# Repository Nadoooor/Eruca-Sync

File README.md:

# Eruca-Sync
-------

--------
## Description:
A smart greenhouse with a closed-loop feedback system that can bring stability automatically to the system by itself. It focuses on green leafy plants and on three parameters. <br>

* Light intensity
* Soil moisture
* Temprature<br>

It has actuators that are responible of making the anti-changes that reverse any changes that occur in the environment, like temperature rise, soil drought, and over-light on the green leafy plants.<br>

### Why I am making this:
I made this because there are plants that I really want to try, but I can't plant them in my home because there is no suitable environment for them. So, the project will provide these plants with their suitable environment. For Example, around my home, I can't plant Eruca (Arugula) because of the direct sunlight and the high temperature. I really want to try planting Arugula, so I thought about how to plant it around my home, but with minimal effort. So, I got this idea to make a self-balancing environment for the Arugula or any plant species. 

### Highlight
The light mechanism is the most highlighted actuator here. It is composed of two servos and two pips, which rotate with each other to change different light transmissivity layers to increase the light intensity coming from the sun or decrease it.

## How it works:

1. First, just plug the power plug into any 220V power source. 
2. The screen will light up, asking which plant species you are planting. 
3. Choose the plant species, and that's it.
4. Leave it on its own; it will show you the real-time parameter readings as it is waiting for any changes to power up the actuators.

## Some photos of the project:

### PCB:<br>

### 3D PCB:<br>

### Schematic:

### 3D design:

<br>
<br>
<br>

### IRL Photo:

> [!NOTE]
> Here you are the [Onshape Docs](https://cad.onshape.com/documents/9a096ebca3b52eda8b421bd5/w/291a79fda487721e4172dde6/e/f2d4edb63e0c7f47e937ec7d).
> Also the build journal [here](Docs/Build_Journal.md)

### Fallout Zine  :
<br>

## BOM (Bill of Materials)

---------------------------------------------
| Item Name                                                        | purchase links                                                                                                                                                                                                                                                                                                                                                                                                                                                                                                                                                                                                                                                                                                           | Quantity      | Price Per Unit | Total  |
|------------------------------------------------------------------|----------------------------------------------------------------------------------------------------------------------------------------------------------------------------------------------------------------------------------------------------------------------------------------------------------------------------------------------------------------------------------------------------------------------------------------------------------------------------------------------------------------------------------------------------------------------------------------------------------------------------------------------------------------------------------------------------------------|---------------|----------------|--------|
| FS5106R Servo Motor 360° Continuous 6 kg.cm Plastic Gears        | [Link](https://www.ram-e-shop.com/shop/servo-fs5106r-fs5106r-servo-motor-360deg-continuous-6-kg-cm-plastic-gears-7122)                                                                                                                                                                                                                                                                                                                                                                                                                                                                                                                                                                                         | 2             | $7.4           | $14.8  |
| AM-2320 Temperature & Humidity Calibrated Sensor                 | [Link](https://www.ram-e-shop.com/shop/sen-am2320-am-2320-temperature-humidity-calibrated-sensor-asair-r-original-brand-7776)                                                                                                                                                                                                                                                                                                                                                                                                                                                                                                                                                                                  | 1             | $3.28          | $3.28  |
| NeoPixel Stick 8-bit WS2812 5050 RGB LED                         | [Link](https://www.ram-e-shop.com/shop/kit-ws2812-8-5050-strip-neopixel-stick-8-bit-ws2812-5050-rgb-led-driver-development-board-8257)                                                                                                                                                                                                                                                                                                                                                                                                                                                                                                                                                                         | 6             | $0.84          | $5.04  |
| Capacitive Analog Soil Moisture Sensor V2.0                      | [Link](https://www.ram-e-shop.com/shop/sen-soil-c-capacitive-analog-soil-moisture-sensor-v2-0-sku-soil-c-8116)                                                                                                                                                                                                                                                                                                                                                                                                                                                                                                                                                                                                 | 1             | $1.87          | $1.87  |
| BH1750 Light Calibrated Sensor                                   | [Link](https://ar.aliexpress.com/item/1005009671465215.html?spm=a2g0o.productlist.main.1.395dPm6FPm6Fzx&algo_pvid=c5de86c0-2d13-4ff4-8794-4309014eb837&algo_exp_id=c5de86c0-2d13-4ff4-8794-4309014eb837-0&pdp_ext_f=%7B%22order%22%3A%22471%22%2C%22spu_best_type%22%3A%22price%22%2C%22eval%22%3A%221%22%2C%22fromPage%22%3A%22search%22%7D&pdp_npi=6%40dis%21EGP%21426.75%21110.40%21%21%2155.72%2114.42%21%40214100f417734488518621569e56b7%2112000049823605481%21sea%21EG%210%21ABX%211%210%21n_tag%3A-29910%3Bd%3A2e304f5e%3Bm03_new_user%3A-29895%3BpisId%3A5000000197840371&curPageLogUid=4LlmP7toFGiX&utparam-url=scene%3Asearch%7Cquery_from%3A%7Cx_object_id%3A1005009671465215%7C_p_origin_prod%3A) | 5             | $1.31          | $6.55  |
| Water Pump 3-6Vdc Mini 120L/H                                    | [Link](https://www.ram-e-shop.com/shop/dc-pump-6vdc-water-pump-3-6vdc-mini-120l-h-7422)                                                                                                                                                                                                                                                                                                                                                                                                                                                                                                                                                                                                                        | 1             | $0.84          | $0.84  |
| Thermoelectric Cooler 40x40mm - Peltier                          | [Link](https://www.ram-e-shop.com/shop/sf10080-thermoelectric-cooler-40x40mm-peltier-6726)                                                                                                                                                                                                                                                                                                                                                                                                                                                                                                                                                                                                                     | 1             | $2.81          | $2.81  |
| Aluminum Heatsink HS.13 Size 40x40x11 mm                         | [Link](https://www.ram-e-shop.com/shop/hs13-aluminum-heatsink-hs-13-size-40x40x11-mm-7713)                                                                                                                                                                                                                                                                                                                                                                                                                                                                                                                                                                                                                     | 1             | $0.52          | $0.52  |
| Kit MOSFET 15A 400W - Trigger Switch Drive Module                | [Link](https://www.ram-e-shop.com/shop/kit-mosfet-15a-400w-kit-mosfet-15a-400w-trigger-switch-drive-module-with-pwm-regulator-control-8008)                                                                                                                                                                                                                                                                                                                                                                                                                                                                                                                                                                    | 5             | $0.84          | $4.22  |
| PC Old Power Supply - 200W                                       | [Link](https://www.dubizzle.com.eg/en/electronics-home-appliances/computers-accessories/q-power-supply/)                                                                                                                                                                                                                                                                                                                                                                                                                                                                                                                                                                                                       | 1             | $2             | $2     |
| Old PC CPU Cooler with its Fan                                   | [Link](https://www.dubizzle.com.eg/en/ad/amd-cpu-stock-fan-ID207435960.html)                                                                                                                                                                                                                                                                                                                                                                                                                                                                                                                                                                                                                                   | 1             | $5.62          | $5.62  |
| Old PC Fan 12cm                                                  | [Link](https://www.dubizzle.com.eg/en/ad/%D9%85%D8%B1%D9%88%D8%AD%D8%A9-%D8%A7%D9%84%D9%83%D9%85%D8%A8%D9%8A%D9%88%D8%AA%D8%B1-pc-case-fan-ID207415788.html)                                                                                                                                                                                                                                                                                                                                                                                                                                                                                                                                                   | 1             | $1.56          | $1.56  |
| Water Container (Any bottle or box)                              | [Link](https://www.amazon.eg/-/en/elyassin-plastic-food-container-size/dp/B0C4K14QZV/ref=asc_df_B0C4K14QZV?mcid=f83f3f40348c3aca81581fd755d29a68&tag=egoshpadde-21&linkCode=df0&hvadid=725177773393&hvpos=&hvnetw=g&hvrand=9898077824252821614&hvpone=&hvptwo=&hvqmt=&hvdev=c&hvdvcmdl=&hvlocint=&hvlocphy=9112388&hvtargid=pla-2235574628331&psc=1&language=en_AE&gad_source=1)                                                                                                                                                                                                                                                                                                                               | 1             | $1.3           | $1.3   |
| Wood with the dimensions (all the dimensions are in the onshape) | Bro any Cabinetmaker you don't need a link for that but [At least this will help](https://goodwood.com.eg/en/new-details.php?id=5973) *(For me i used recycled wood from my school)*                                                                                                                                                                                                                                                                                                                                                                                                                                                                                                                           | ~~~           | Vary           | Vary   |
| LCD TFT 2.8 inch Touch Display with ILI9341 Driver 8bit Parallel | [Link](https://www.ram-e-shop.com/shop/kit-lcd-tft-2-8-touch-lcd-tft-2-8-inch-touch-display-for-arduino-uno-mega2560-8003)                                                                                                                                                                                                                                                                                                                                                                                                                                                                                                                                                                                     | 1             | $12.18         | $12.18 |
| ESP32-S3-N16R8 Development Board WIFI and Bluetooth              | [Link](https://mostelectronic.com/shop/arduino-development-boards/esp32-s3-n16r8-development-board-wifi-and-bluetooth/)                                                                                                                                                                                                                                                                                                                                                                                                                                                                                                                                                                                        | 1             | $14.06         | $14.06 |
| PVC pipes as the rotation axies                                  | As well as the wood (plz don't buy it online it is so cheap out there)                                                                                                                                                                                                                                                                                                                                                                                                                                                                                                                                                                                                                                         | 2 x 0.5 meter | $3             | $6     |
| Plastic baggs or plastic sheets                                  | Recycled as well                                                                                                                                                                                                                                                                                                                                                                                                                                                                                                                                                                                                                                                                                               | ~~~           | ~~~            | ~~~    |
| Jumper Wires                                                     | [Link](https://www.ram-e-shop.com/shop/ph61-mm-20cm-ph61-20cm-male-to-male-40-jumper-wires-set-7094)                                                                                                                                                                                                                                                                                                                                                                                                                                                                                                                                                                                                           | 60            | $0.019         | $1.14  |
| Some Nails                                                       | The same place as the pipes                                                                                                                                                                                                                                                                                                                                                                                                                                                                                                                                                                                                                                                                                    | 30            | $0.027         | $0.8   |
| MDF Fast Adhesive Glue                                           | [Link](https://www.amazon.eg/-/en/Akfix-705-Universal-Fast-Adhesive/dp/B07MCQWCQV/ref=sr_1_1?crid=JMZABOFI5Q59&dib=eyJ2IjoiMSJ9.hP0t54WhPBYIvN8RvywzGqQzmqMzmlUrEu0KOEwCDyFlItWe3BiQIYQlq1yIXfjjS0ecLwjxcFoKdVqo_EhPNP86NvI5iyCbqhyLeSCvPZjHmqx9VoXkYTefGrMRnnf0KyayZ9sEV9TGBmlidY9Lgcd1uuuBjttEH5GCcZUDynxih5r3d0zRSV9uq8jcek3OShltEkHc4jghPpo9axMgmGLadUvlVsrWXO3OFKS7u-6tiLPWEWCTFn07oKDck0iPlYYDRP0nvmkYCfUdia9bh31qRD-YmvvLp57fdF0v_p4.mqZp0Uo2UkpAlmg85BgYv_H7G6fkgERg_iH2WGTqdU0&dib_tag=se&keywords=MDF+glue&qid=1779096887&sprefix=mdf+glue%2Caps%2C190&sr=8-1)                                                                                                                                       | 2             | $3.18          | $6.36  |
| PCB | [Link](https://uge-one.com/pcb-print-design/?srsltid=AfmBOopBK8awYYikG2a9qXKbW5DigASPA7Sdrr7dOJ97qQsz4a_aT9M1) | 1 | $20 | $20|
| Shipping                                                         | ~~~~~~~~~~                                                                                                                                                                                                                                                                                                                                                                                                                                                                                                                                                                                                                                                                                                     | ~~~           | ~~~            | $6.74  |
| Total                                                            | ~~~~~~~~~~                                                                                                                                                                                                                                                                                                                                                                                                                                                                                                                                                                                                                                                                                                     | ~~~           | ~~~            | $117.69 |

## How to build the Code:
1. Install PIO (PlatformIO) and clone the repo
2. Open the Eruca-Sync-Code folder, which has the source code in PlatformIO VS Code.
3. Do whatever you want, edit, add, remove, etc.
4. Just click the check mark down there in VS Code to build the code into a .bin and .elf files.
5. Or just click the arrow icon while connecting the ESP to the PC/Laptop to directly compile and upload the code.
6. Enjoy ;)

## How to build the structure:
1. Get wood with the right dimensions(You will find them in the Onshape docs).
2. For the arc on top of the planting area, you can laser cut them along the motor and pipe holders
3. Use the Nails to install all four columns (You can, like, put the nail in its place on the base, and then take it back and cut its head and put it again, and then install the column using a hammer as I did with mine)
4. When you finish the structure using nails and wood, you can then take the fan part, and first you should cut a thin wood rectangle piece(like in the 3D), and then nail the two short columns on top of its sides.
5. Screw the PC fan and the PC cooling part 
6. After that, install the full piece with the same method as the regular columns.
7. Install the wooden planting area, which has the arc and columns on top. (with the same techniques).
8. Put the light sensor and the temperature in the middle of any side of the planting area. (you can use two lil screw or MDF glue).
9. Put the soil in the planting area (And place the soil moisture sensor in the middle of it).
10. You can connect the four outer columns with tall wooden horizontal pieces to make it stable if it is not.
11. Make two identical Rectangles for the roof with the dimensions.
12. Place them at a 30-degree angle from the horizontal so they can make a triangle with each other.
13. Install the Control Panel box on the front side of the structure at an angle of 45 degrees with two small wooden pieces under it to make it stable. (Glue the box to those pieces with MDF and use a nail on the other side in the two little columns.
14. Add the PCB and wire everything to its place on the PCB.
15. Place the power supply and the water container.
16. Use plastic bags or acrylic sheets to cover the greenhouse.
17. Upload the code 
18. That's it, enjoy. ❤️
-----------------

# Made with ❤️ By Nadooor

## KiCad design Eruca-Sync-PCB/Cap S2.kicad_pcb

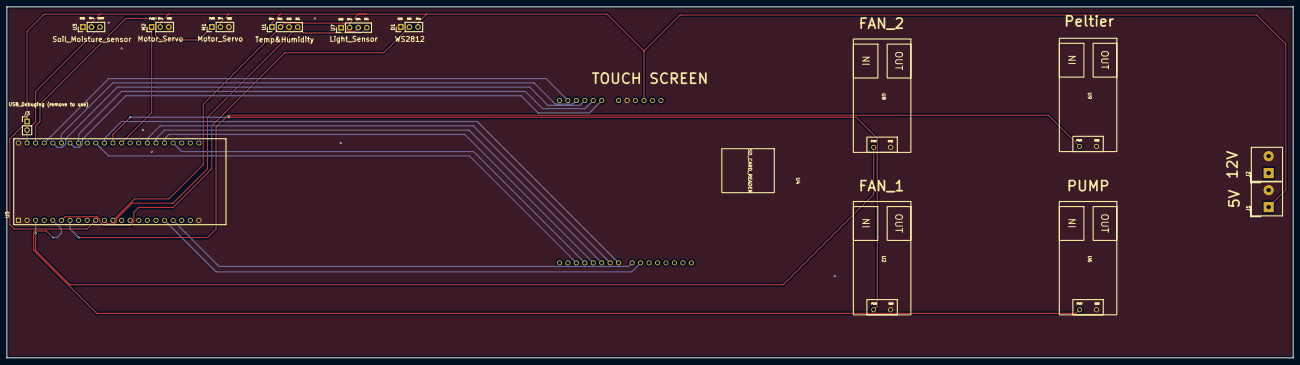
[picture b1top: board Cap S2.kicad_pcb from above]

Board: 2 copper layers, 380.2 x 103.7 mm, 15 parts (0 on the bottom side), 27 nets.

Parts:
D1: WS2812; PinHeader_1x03_P2.54mm_Vertical
J1: 5v&GND; Altech_AK100_1x02_P5.00mm
J2: 12v&GND; Altech_AK100_1x02_P5.00mm
J3: USB_Debuging (remove to use); PinHeader_1x02_P2.54mm_Vertical
M1, M2: Motor_Servo; PinHeader_1x03_P2.54mm_Vertical
U1: Temp&Humidity; PinHeader_1x04_P2.54mm_Vertical
U2: Fan1; MOSFET_KIT
U3: Soil_Moisture_sensor; PinHeader_1x03_P2.54mm_Vertical
U4: TFT_ILI9341_arduino_Sheid; TFT_SCREEN
U5: ESP32-S3; ESP32-S3-DEVKITC-1
U6: Pump; MOSFET_KIT
U7: Light_Sensor; PinHeader_1x04_P2.54mm_Vertical
U8: Fan2; MOSFET_KIT
U9: Platier; MOSFET_KIT

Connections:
5v+: D1.3 (VCC), J1.1, J3.1, M1.2 (+), M2.2 (+), U1.1 (VDD), U3.2 (VCC), U4.10 (5V), U7.2 (VCC)
Fan1: U2.2 (PWM+), U5.33 (GPIO18)
Fan2: U5.3 (GPIO19/USB_D-), U8.2 (PWM+)
GND: D1.1 (VSS), J1.2, J2.2, M1.3 (-), M2.3 (-), U1.3 (GND), U2.1 (GND), U3.1 (GND), U4.8 (GND), U5.1 (GND), U5.2 (GND), U5.22 (GND), U5.44 (GND), U6.1 (GND), U7.1 (GND), U8.1 (GND), U9.1 (GND)
LCD0: U4.20 (LCD_D0), U5.19 (GPIO1)
LCD1: U4.19 (LCD_D1), U5.18 (GPIO2)
LCD2: U4.26 (LCD_D2), U5.35 (GPIO3)
LCD3: U4.25 (LCD_D3), U5.26 (GPIO4)
LCD4: U4.24 (LCD_D4), U5.27 (GPIO5)
LCD5: U4.23 (LCD_D5), U5.28 (GPIO6)
LCD6: U4.22 (LCD_D6), U5.29 (GPIO7)
LCD7: U4.21 (LCD_D7), U5.34 (GPIO8)
LCD_CS: U4.3 (LCD_CS), U5.39 (GPIO11)
LCD_RD: U4.6 (LCD_RD), U5.38 (GPIO10)
LCD_RS: U4.4 (LCD_RS), U5.40 (GPIO12)
LCD_RST: U4.2 (LCD_RST), U5.41 (GPIO13)
LCD_WR: U4.5 (LCD_WR), U5.37 (GPIO9)
Mois_Dout: U3.3 (AUOUT), U5.10 (GPIO35)
unnamed: J3.2, U5.43 (VDDA)
unnamed: U5.23 (VDD3P3), U5.24 (VDD3P3)
Platier: U5.7 (SPICLK_N), U9.2 (PWM+)
Pump: U5.5 (GPIO21), U6.2 (PWM+)
RGB: D1.2 (DIN), U5.6 (SPICLK_P)
SCL_light: U1.4 (SCL), U5.11 (GPIO36), U7.4 (SCL)
SDA_light: U1.2 (SDA), U5.12 (GPIO37), U7.3 (SDA)
Servo1: M1.1 (PWM), U5.42 (GPIO14)
Servo2: M2.1 (PWM), U5.32 (GPIO17)

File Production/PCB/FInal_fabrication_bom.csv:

Designator,Footprint,Quantity,Value,LCSC Part #
D1,PinHeader_1x03_P2.54mm_Vertical,1,WS2812,
J1,Altech_AK100_1x02_P5.00mm,1,5v&GND,
J2,Altech_AK100_1x02_P5.00mm,1,12v&GND,
J3,PinHeader_1x02_P2.54mm_Vertical,1,USB_Debuging (remove to use),
"M1, M2",PinHeader_1x03_P2.54mm_Vertical,2,Motor_Servo,
U1,PinHeader_1x04_P2.54mm_Vertical,1,Temp&Humidity,
U2,MOSFET_KIT,1,Fan1,
U3,PinHeader_1x03_P2.54mm_Vertical,1,Soil_Moisture_sensor,
U4,TFT_SCREEN,1,TFT_ILI9341_arduino_Sheid,
U5,ESP32-S3-DEVKITC-1,1,ESP32-S3,
U6,MOSFET_KIT,1,Pump,
U7,PinHeader_1x04_P2.54mm_Vertical,1,Light_Sensor,
U8,MOSFET_KIT,1,Fan2,
U9,MOSFET_KIT,1,Platier,

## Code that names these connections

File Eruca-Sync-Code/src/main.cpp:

#include <Arduino.h>
#include <Wire.h>
#include <TFT_eSPI.h>       
#include <TouchScreen.h>
#include <BH1750.h>
#include <ESP32Servo.h>
#include <Adafruit_NeoPixel.h>
#include <Adafruit_AM2320.h>
  

#define YP 12 
#define XM 11 
#define YM 1  
#define XP 2  

#define I2C_SDA 37
#define I2C_SCL 36

#define Peliter_pin 48
#define NEOs_pin 47
#define FAN1_pin 16
#define FAN2_pin 17
#define PUMP_pin 21
#define Soil_pin 35
#define ServoL_pin 14
#define ServoR_pin 17

TouchScreen ts = TouchScreen(XP, YP, XM, YM, 300);
TFT_eSPI tft = TFT_eSPI();
BH1750 lightMeter;
Adafruit_AM2320 am;
Servo ServoL;
Servo ServoR;
Adafruit_NeoPixel pixels(48, NEOs_pin, NEO_GRB + NEO_KHZ800);
float currentTemp = 0;
float currentMoist = 0;
float currentLux = 0;

bool tempStatus = false;
bool moistStatus = false;
bool lightStatus = false;

enum SYSMOD{MENU, ARGULA, SPINACH};

SYSMOD sysmod = MENU;

//Parameters  and limits for the feedback system

int mode = 0; //0 for spinach, 1 for argula

float targetTemp = 0;
float min_temp = 0; 
float max_temp = 0;
float targetMoist = 0;
float targetlux = 0; 
float min_lux = 0;
float max_lux = 0;
int irrigation_time = 0;

float Argula_targetTemp = 20.0;
float Argula_min_temp = 18.0; 
float Argula_max_temp = 22.0;
float Argula_targetMoist = 60.0;
float Argula_targetlux = 10800; 
float Argula_min_lux = 9990;
float Argula_max_lux = 11610;
int Argula_irrigation_time = 11800;
int currentlevel = 0; 

//temp
float Spinach_targetTemp = 25.0;
float Spinach_min_temp = 23.0; 
float Spinach_max_temp = 27.0;

//moisture
float Spinach_targetMoist = 70.0;
//light
float Spinach_targetlux = 8100; 
float Spinach_min_lux = 7290;
float Spinach_max_lux = 8910;
float Spinach_irrigation_time = 18610;



float calibed_soil(float raw){
    float calibed = map(raw,3241,1491,0,100);
    if (calibed < 0){
      calibed = 0;
    }
    else if (calibed > 100){
      calibed = 100;
    }
    
      return calibed;
    
}

float calibed_lux(float raw){
    return 0.9985 * raw;
}

float calibed_temp(float raw){
    return 1.054 *raw - 0.2272;
}


float measurePtemp(class Adafruit_AM2320 am){
    return calibed_temp(am.readTemperature());
}

float measurelight(class BH1750 lightMeter){
    return calibed_lux(lightMeter.readLightLevel());
}
float measuremoist(){
    return calibed_soil(analogRead(Soil_pin));
}


void statics(){
    tft.fillScreen(TFT_BLACK);
    tft.fillRect(0, 0, 320, 35, TFT_NAVY);
    tft.setTextColor(TFT_WHITE);
    tft.drawCentreString("Eruca Sync", 160, 8, 2);
    tft.drawFastHLine(0, 85, 300, TFT_SILVER);
    tft.drawFastHLine(0, 140, 300, TFT_SILVER);

    tft.drawFastVLine(160, 45, 145, TFT_SILVER);
    tft.setTextColor(TFT_WHITE);
    tft.drawString("TEMP:",15, 45, 2);
    tft.drawString("MOIST:", 170, 45, 2);
    tft.drawString("LUX:", 15, 95, 2);
    tft.drawString("ACTUATORS:", 170, 95, 2);
}


void menu(){
    tft.fillScreen(TFT_BLACK);
    tft.setTextColor(TFT_WHITE);
    tft.drawCentreString("Select Plant", 160, 40, 4);


    tft.fillRect(20, 100, 130, 80, TFT_DARKGREEN);
    tft.fillRect(20,100,130,80, TFT_WHITE);
    tft.drawCentreString("Argula", 85, 130, 2);

    tft.fillRect(170, 100, 130, 80, TFT_MAROON);
    tft.fillRect(170,100,130,80, TFT_WHITE);  
    tft.drawCentreString("Spinach", 235, 130, 2);  

}


void refreash(){
    tft.setTextColor(TFT_CYAN, TFT_BLACK);
    tft.drawString(String(currentTemp, 1) + " C", 15, 60, 4);
    tft.setTextColor(TFT_BLUE, TFT_BLACK);
    tft.drawString(String(currentMoist, 1) + " %", 170, 60, 4);
    tft.setTextColor(TFT_YELLOW, TFT_BLACK);
    tft.drawString(String(currentLux, 0) + " lx", 15, 110, 4);

    tft.setTextSize(1);
    tft.setTextColor(tempStatus ? TFT_GREEN : TFT_RED, TFT_BLACK);
    tft.drawString(tempStatus ? "Cooling: ON" : "Cooling: OFF", 170, 115, 2);
    tft.setTextColor(moistStatus ? TFT_GREEN : TFT_RED, TFT_BLACK);
    tft.drawString(moistStatus ? "Irrigation: ON" : "Irrigation: OFF", 170, 135, 2);
    tft.setTextColor(lightStatus ? TFT_GREEN : TFT_RED, TFT_BLACK); 
    tft.drawString(lightStatus ? "Shading: ON" : "Shading: OFF", 170, 155, 2);

}



void logic(){
    //temp_logic
    if (mode == 1){
    targetlux = Argula_targetlux;
    targetMoist = Argula_targetMoist;
    targetTemp = Argula_targetTemp;

    max_lux = Argula_max_lux;
    min_lux = Argula_min_lux;

    max_temp = Argula_max_temp;
    min_temp = Argula_min_temp;
    irrigation_time = Argula_irrigation_time;
    }
    else if (mode == 0){
    targetlux = Spinach_targetlux;
    targetMoist = Spinach_targetMoist;
    targetTemp = Spinach_targetTemp;

    max_lux = Spinach_max_lux;
    min_lux = Spinach_min_lux;

    max_temp = Spinach_max_temp;
    min_temp = Spinach_min_temp;

    irrigation_time = Spinach_irrigation_time;
    
}

if(currentTemp > max_temp){
    analogWrite(FAN1_pin, 255);
    analogWrite(FAN2_pin, 255);
    analogWrite(Peliter_pin, 255);
    tempStatus = true;
    
}
else if (currentTemp < min_temp){
    analogWrite(FAN1_pin, 0);
    analogWrite(FAN2_pin, 0);
    analogWrite(Peliter_pin, 0);
    tempStatus = false;
} else {
    Serial.println("There is a problem with the temperature sensor");
}


if (currentMoist < 50 && currentMoist > 10){
    moistStatus = true;
    analogWrite(PUMP_pin, 255);
    delay(irrigation_time);
    analogWrite(PUMP_pin, 0);
    moistStatus = false;
} else if (currentMoist <= 10){
    analogWrite(PUMP_pin, 0);
    moistStatus = false;
} else if (currentMoist >= 85){
    analogWrite(PUMP_pin, 0);
    moistStatus = false;
}

if (currentLux < min_lux && currentLux >= 0){
    if(currentlevel > 0){
        lightStatus = true;
        ServoL.write(45); ServoR.write(135);
        currentlevel--;
        delay(9500);
        ServoL.write(90); ServoR.write(90);
        lightStatus = false;
    
    } else if (currentlevel == 0){
        for (int i = 0; i < 48; i++){
            pixels.setPixelColor(i, pixels.Color(128, 0, 32));
            pixels.show();
            delay(50);
        }
    }

} else if (currentLux > max_lux && currentlevel< 4){
    for (int i = 0; i < 48; i++){
            pixels.setPixelColor(i, pixels.Color(0, 0, 0));
            pixels.show();
            delay(50);
        }
        lightStatus = true;
    ServoL.write(135); ServoR.write(45);
    currentlevel++;
    delay(9500);
    ServoL.write(90); ServoR.write(90);
    lightStatus = false;
} else {
    ServoL.write(90); ServoR.write(90);
    lightStatus = false;
}



}

void setup() {
    Serial.begin(115200);
    tft.init();
    tft.setRotation(3);

    pinMode(Peliter_pin, OUTPUT);
    pinMode(FAN1_pin, OUTPUT);
    pinMode(FAN2_pin, OUTPUT);
    pinMode(PUMP_pin, OUTPUT);
    pinMode(Soil_pin, INPUT);
    pinMode(NEOs_pin, OUTPUT);
    ServoL.attach(ServoL_pin);
    ServoR.attach(ServoR_pin);
    pixels.begin();
    pixels.setBrightness(100);

    Wire.begin(I2C_SDA, I2C_SCL, 100000);
    am.begin();
    lightMeter.begin(BH1750::CONTINUOUS_HIGH_RES_MODE, 0x23, &Wire);
    menu();
}

void loop() {
    if (sysmod == MENU){
        TSPoint p = ts.getPoint();

        pinMode(XP, OUTPUT);
        pinMode(YP, OUTPUT);

        if (p.z > ts.pressureThreshhold){

            int16_t x_calibed = map(p.x, 390, 3683, 0, 320);
            int16_t y_calibed = map(p.y, 3408, 471, 0, 240);

            if (x_calibed > 20 && x_calibed < 150 && y_calibed > 100 && y_calibed < 180){
                mode = 1;
                sysmod = ARGULA;
                tft.fillScreen(TFT_BLACK);
                statics();
            } else if (x_calibed > 170 && x_calibed < 300 && y_calibed > 100 && y_calibed < 180){
                mode = 0;
                sysmod = SPINACH;
                tft.fillScreen(TFT_BLACK);
                statics();
            }

        }





    }else {
    float Stemp = 0;
    float Slux = 0;
    float Smoist = 0;

    for (int i = 0; i < 3; i++){
        Stemp += measurePtemp(am);
        Slux += measurelight(lightMeter);
        Smoist += measuremoist();
        delay(1000);
    }
    currentTemp = Stemp/3;
    currentLux = Slux/3;
    currentMoist = Smoist/3;
    refreash();


    logic();
    }
}

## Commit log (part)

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2026-05-18 Init PIO project
2026-05-18 just changed the folder name
2026-05-18 Wrote all the Logic and the hardcoded parameters
2026-05-18 Finished also the UI of the screen and touch functionality to choose the mode
2026-05-18 built the firmware
2026-05-18 Added the BOM
2026-05-18 Added the PCB and putted the production files in one folder
2026-05-18 BOM edit
2026-05-18 Added photos and made the Readme
2026-05-18 Oops,, forgot the schematic photo
2026-05-18 Added the onshape docs to the Readme
2026-05-18 Fix markdown link syntax in README.md
2026-05-18 Adding some scintefic content i made with my school team
2026-05-18 Added build instrucions
2026-05-18 Well, gitignoure shouldn't include .pio folder
2026-05-20 Fix typos and improve grammar in README.md
    Corrected spelling and grammatical errors in the README.
2026-05-20 Added Fallout Zine, yayyyy it is all ready
2026-05-20 remove a unneeded br
2026-05-20 Update total cost and add the forgotten PCB in BOM.md
    Updated total cost to reflect the addition of PCB.
2026-05-20 Add PCB to BOM and update total cost
2026-05-20 Added credits
2026-05-20 Update BOM.csv to change 'Store' to 'Links'
2026-05-20 Fix typos and enhance project description in README
    Corrected typos and improved clarity in the project description and instructions.
2026-05-20 fix organization to be good with fallout review
2026-05-20 deleting unwanted things
2026-05-20 Change 'Links' header to 'purchase links' in BOM.csv
    Updated the column header from 'Links' to 'purchase links' in BOM.csv.
2026-05-20 Update purchase links in BOM documentation
2026-05-20 Revise BOM.csv with new links and item details
    Updated links and descriptions for several items in the BOM.
2026-05-20 hope it works now
2026-05-20 Add BOM section to README with item details
    Added a Bill of Materials section with item details, purchase links, quantities, and prices.
2026-05-20 Revise BOM.csv with new items and formatting fixes
    Updated BOM.csv to include new items and correct formatting.
2026-05-20 Modify PCB entry in BOM.csv
    Updated PCB entry to include quantity and corrected format.
2026-05-20 Update URL for Aluminum Heatsink product
2026-05-22 Added 3D design exported .STEP file
2026-06-02 Build_Journal started writing
2026-06-03 Writing build journal
2026-06-04 Wrote the build journal
2026-06-04 fixed this photo
2026-06-06 fix the sum of the total hours
2026-06-26 Fix typo in '3D design' section header
